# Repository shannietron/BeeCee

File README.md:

# BeeCee
BeeCee a USB C to microUSB adapter that won't fry your device

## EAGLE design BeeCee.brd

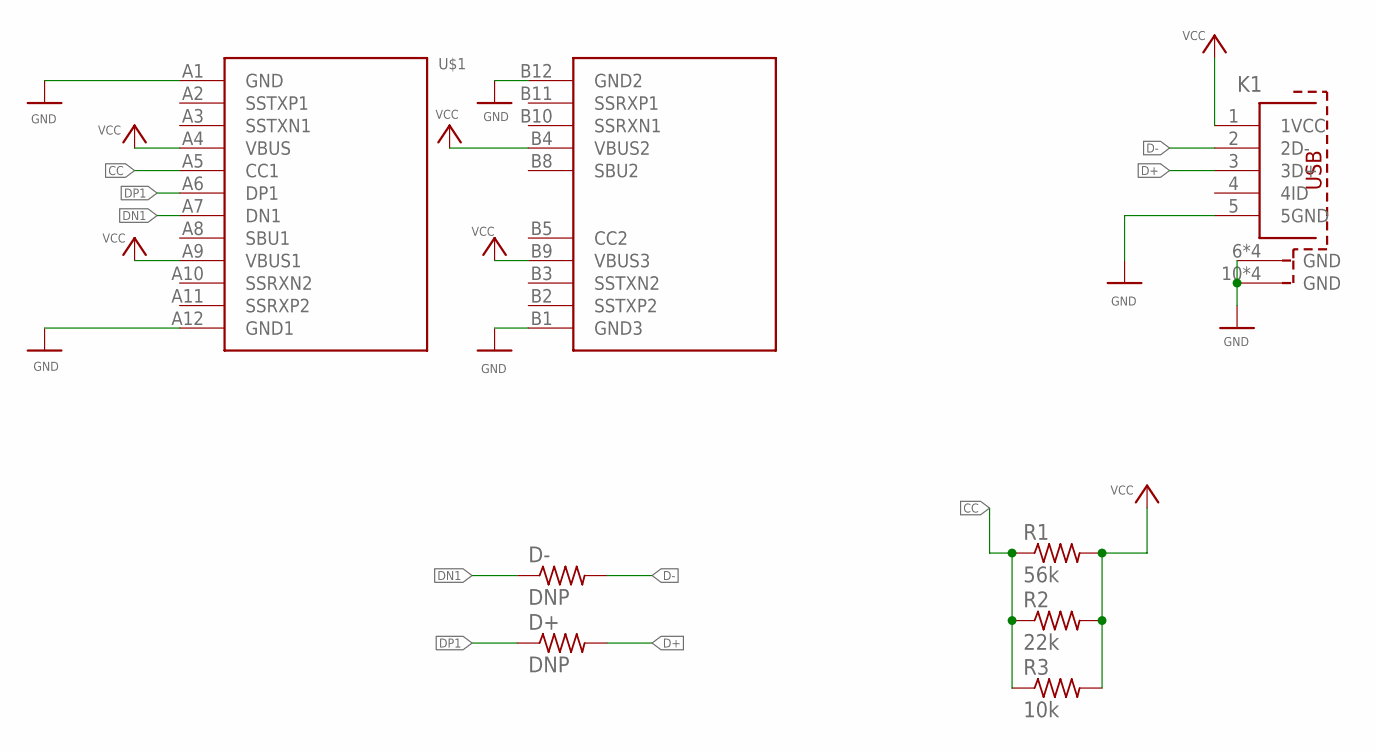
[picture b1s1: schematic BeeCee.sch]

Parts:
D+: DNP; R0805
D-: DNP; R0805
K1: 629105150921
R1: 56k; R0805
R2: 22k; R0805
R3: 10k; R0805
U$1: 632712000011(T); 632712000011

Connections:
CC: R1.1, R2.1, R3.1, U$1.A5 (CC1)
D+: D+.2, K1.3 (3D+)
D-: D-.2, K1.2 (2D-)
DN1: D-.1, U$1.A7 (DN1)
DP1: D+.1, U$1.A6 (DP1)
GND: K1.5 (5GND), K1.6 (GND), K1.7 (GND), K1.8 (GND), K1.9 (GND), K1.10 (GND), K1.11 (GND), K1.12 (GND), K1.13 (GND), U$1.A1 (GND), U$1.A12 (GND1), U$1.B1 (GND3), U$1.B12 (GND2)
VCC: K1.1 (1VCC), R1.2, R2.2, R3.2, U$1.A4 (VBUS), U$1.A9 (VBUS1), U$1.B4 (VBUS2), U$1.B9 (VBUS3)

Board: 2 copper layers, 7 parts (0 on the bottom side), 7 nets, no tracks yet.

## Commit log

2016-03-10 init
2016-03-10 finalized USB C & AB connectors
2016-03-21 finished up the schematics, gave up on finding a small enough selector switch
2016-03-21 created board from schematic
2016-03-21 preliminary component layout. Might be able to squeeze in a selector switch

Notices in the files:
parts and their libraries:
Eagle_INPUT_OUTPUT_CONNECTORS_rev15d: Copyright: Würth Elektronik
